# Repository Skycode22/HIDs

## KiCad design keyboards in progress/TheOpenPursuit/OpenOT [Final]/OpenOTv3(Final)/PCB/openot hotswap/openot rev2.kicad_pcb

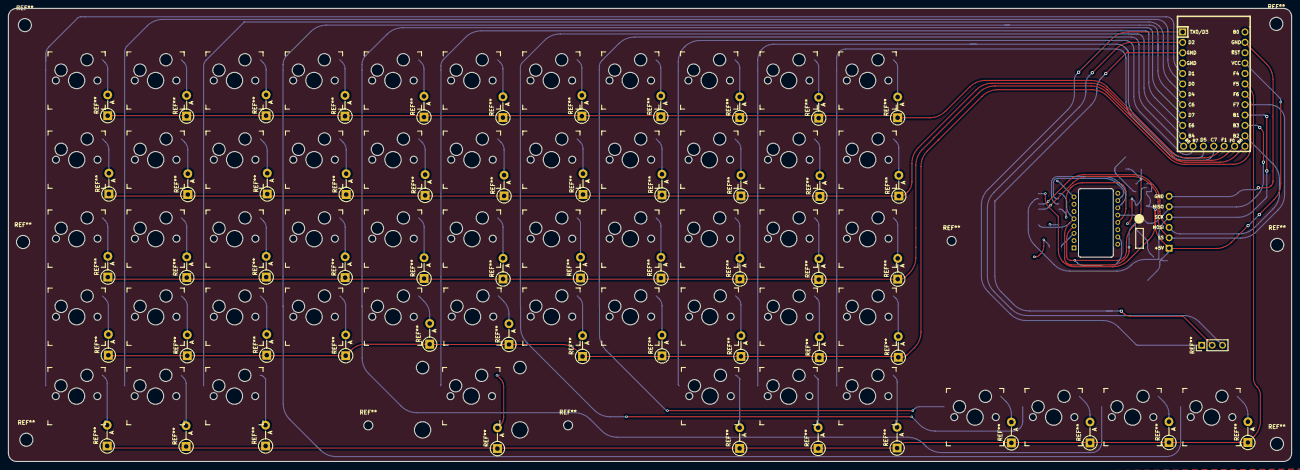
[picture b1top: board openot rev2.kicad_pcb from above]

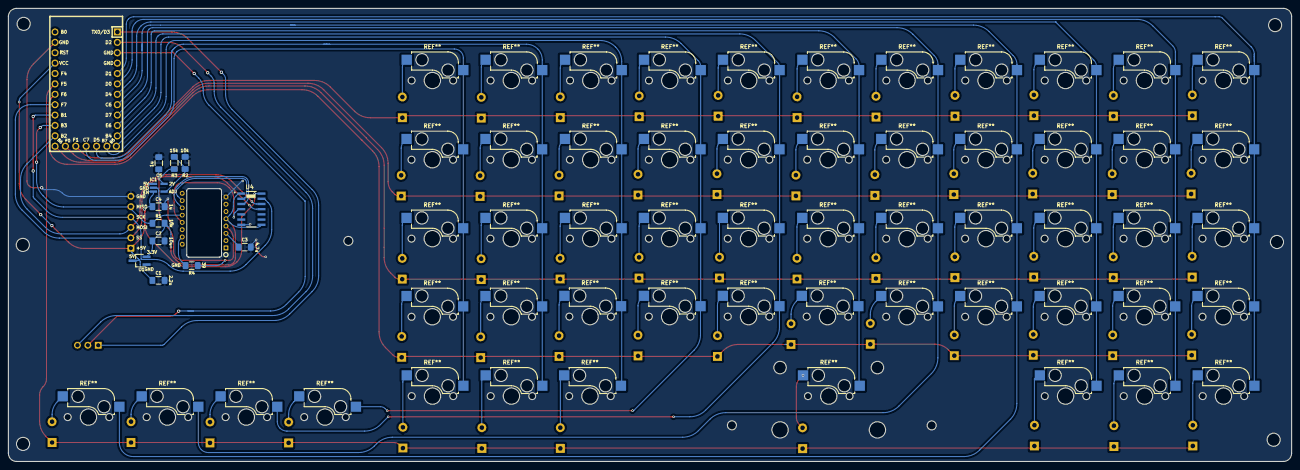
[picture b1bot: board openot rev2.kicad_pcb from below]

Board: 2 copper layers, 313.8 x 110.8 mm, 15 parts (13 on the bottom side), 14 nets.

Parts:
C1: 2.2uF; C_1206_3216Metric_Pad1.42x1.75mm_HandSolder
C2: 10uF; C_1206_3216Metric_Pad1.42x1.75mm_HandSolder
C3: 4.7uF; C_1206_3216Metric_Pad1.42x1.75mm_HandSolder
C4, C5: 1uF; C_1206_3216Metric_Pad1.42x1.75mm_HandSolder
IC1: AP7335-WG-7; AP7331
J1: Conn_01x06_Female; PinHeader_1x06_P2.54mm_Vertical
R1, R2: 10k; R_1206_3216Metric_Pad1.42x1.75mm_HandSolder
R3: 15k; R_1206_3216Metric_Pad1.42x1.75mm_HandSolder
R4: 39; R_1206_3216Metric_Pad1.42x1.75mm_HandSolder
U1: Elite-C
U1#2: XC6206P332MR; TSOT-23_HandSoldering
U2: PMW3360DM-T2QU; DIP-16_W10.16mm
U4: TXS0104EDR; SOIC127P600X175-14N

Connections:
GND: C1.2, C2.2, C3.2, C4.2, C5.2, IC1.2 (GND), J1.1, R2.2, U1#2.1 (GND), U2.8 (GND), U4.7 (GND)
MISO: J1.2, R1.2, U2.12 (MISO)
MOSI: U2.11 (MOSI), U4.3 (A2)
MOSI_I: J1.4, U1.14, U4.12 (B2)
NCS: U2.13 (NCS), U4.4 (A3)
NCS_I: J1.5, U4.11 (B3)
unnamed: C3.1, U2.3 (VDDPIX)
unnamed: IC1.4 (ADJ), R2.1, R3.1
unnamed: R4.2, U2.15 (LED_P)
SCLK: U2.10 (SCLK), U4.2 (A1)
SCLK_I: J1.3, U4.13 (B1)
VDD_2V: C5.1, IC1.5 (OUT), R3.2, R4.1, U2.4 (VDD)
VDD_3.3V: C2.1, R1.1, U1#2.2 (VO), U2.5 (VDDIO), U4.1 (VCCA), U4.8 (OE)
VDD_5V: C1.1, C4.1, IC1.1 (IN), IC1.3 (EN), J1.6, U1#2.3 (VI), U4.14 (VCCB)
